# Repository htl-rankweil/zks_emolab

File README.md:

emolab is a new control board hardware with some generic function to run and control
a model car (Carrera 1:24 style) that runs on a Carrera slotcar track.

The boards generic blocks and functionality:

- a Nordic NRF54L15 module form ezurio as core element for communication. preprogrammed with generic SW.
- an Atmega32 processor for easy maintainability by students not familiar with the zephyr system
- both processors interchange information via UART
- the board is supplied from a battery in the range of 10-20V (defined later)
- the processors each have their own LDO as power supply
- an integrated Full Bridge from Toshiba acts as motor driver for speed and direction control
- PWMs can be generated from both cores (selectable via resistor fitting)
- the board has two expansion ports to add further functionality
- the ports have all power lines and a large range of additional IO pins
- I2C and SPI are both available from both cores on the ports. The cores are selected via solder jumper
- The battery voltage can be disconnected from the driver via a PCH Mosfet
- LEDs are provided for each core and to indicate motor supply voltage is on
- The expansion port pins are such that the small standard OLED Display can be fitted directly to have a display either for ATM or from NRF

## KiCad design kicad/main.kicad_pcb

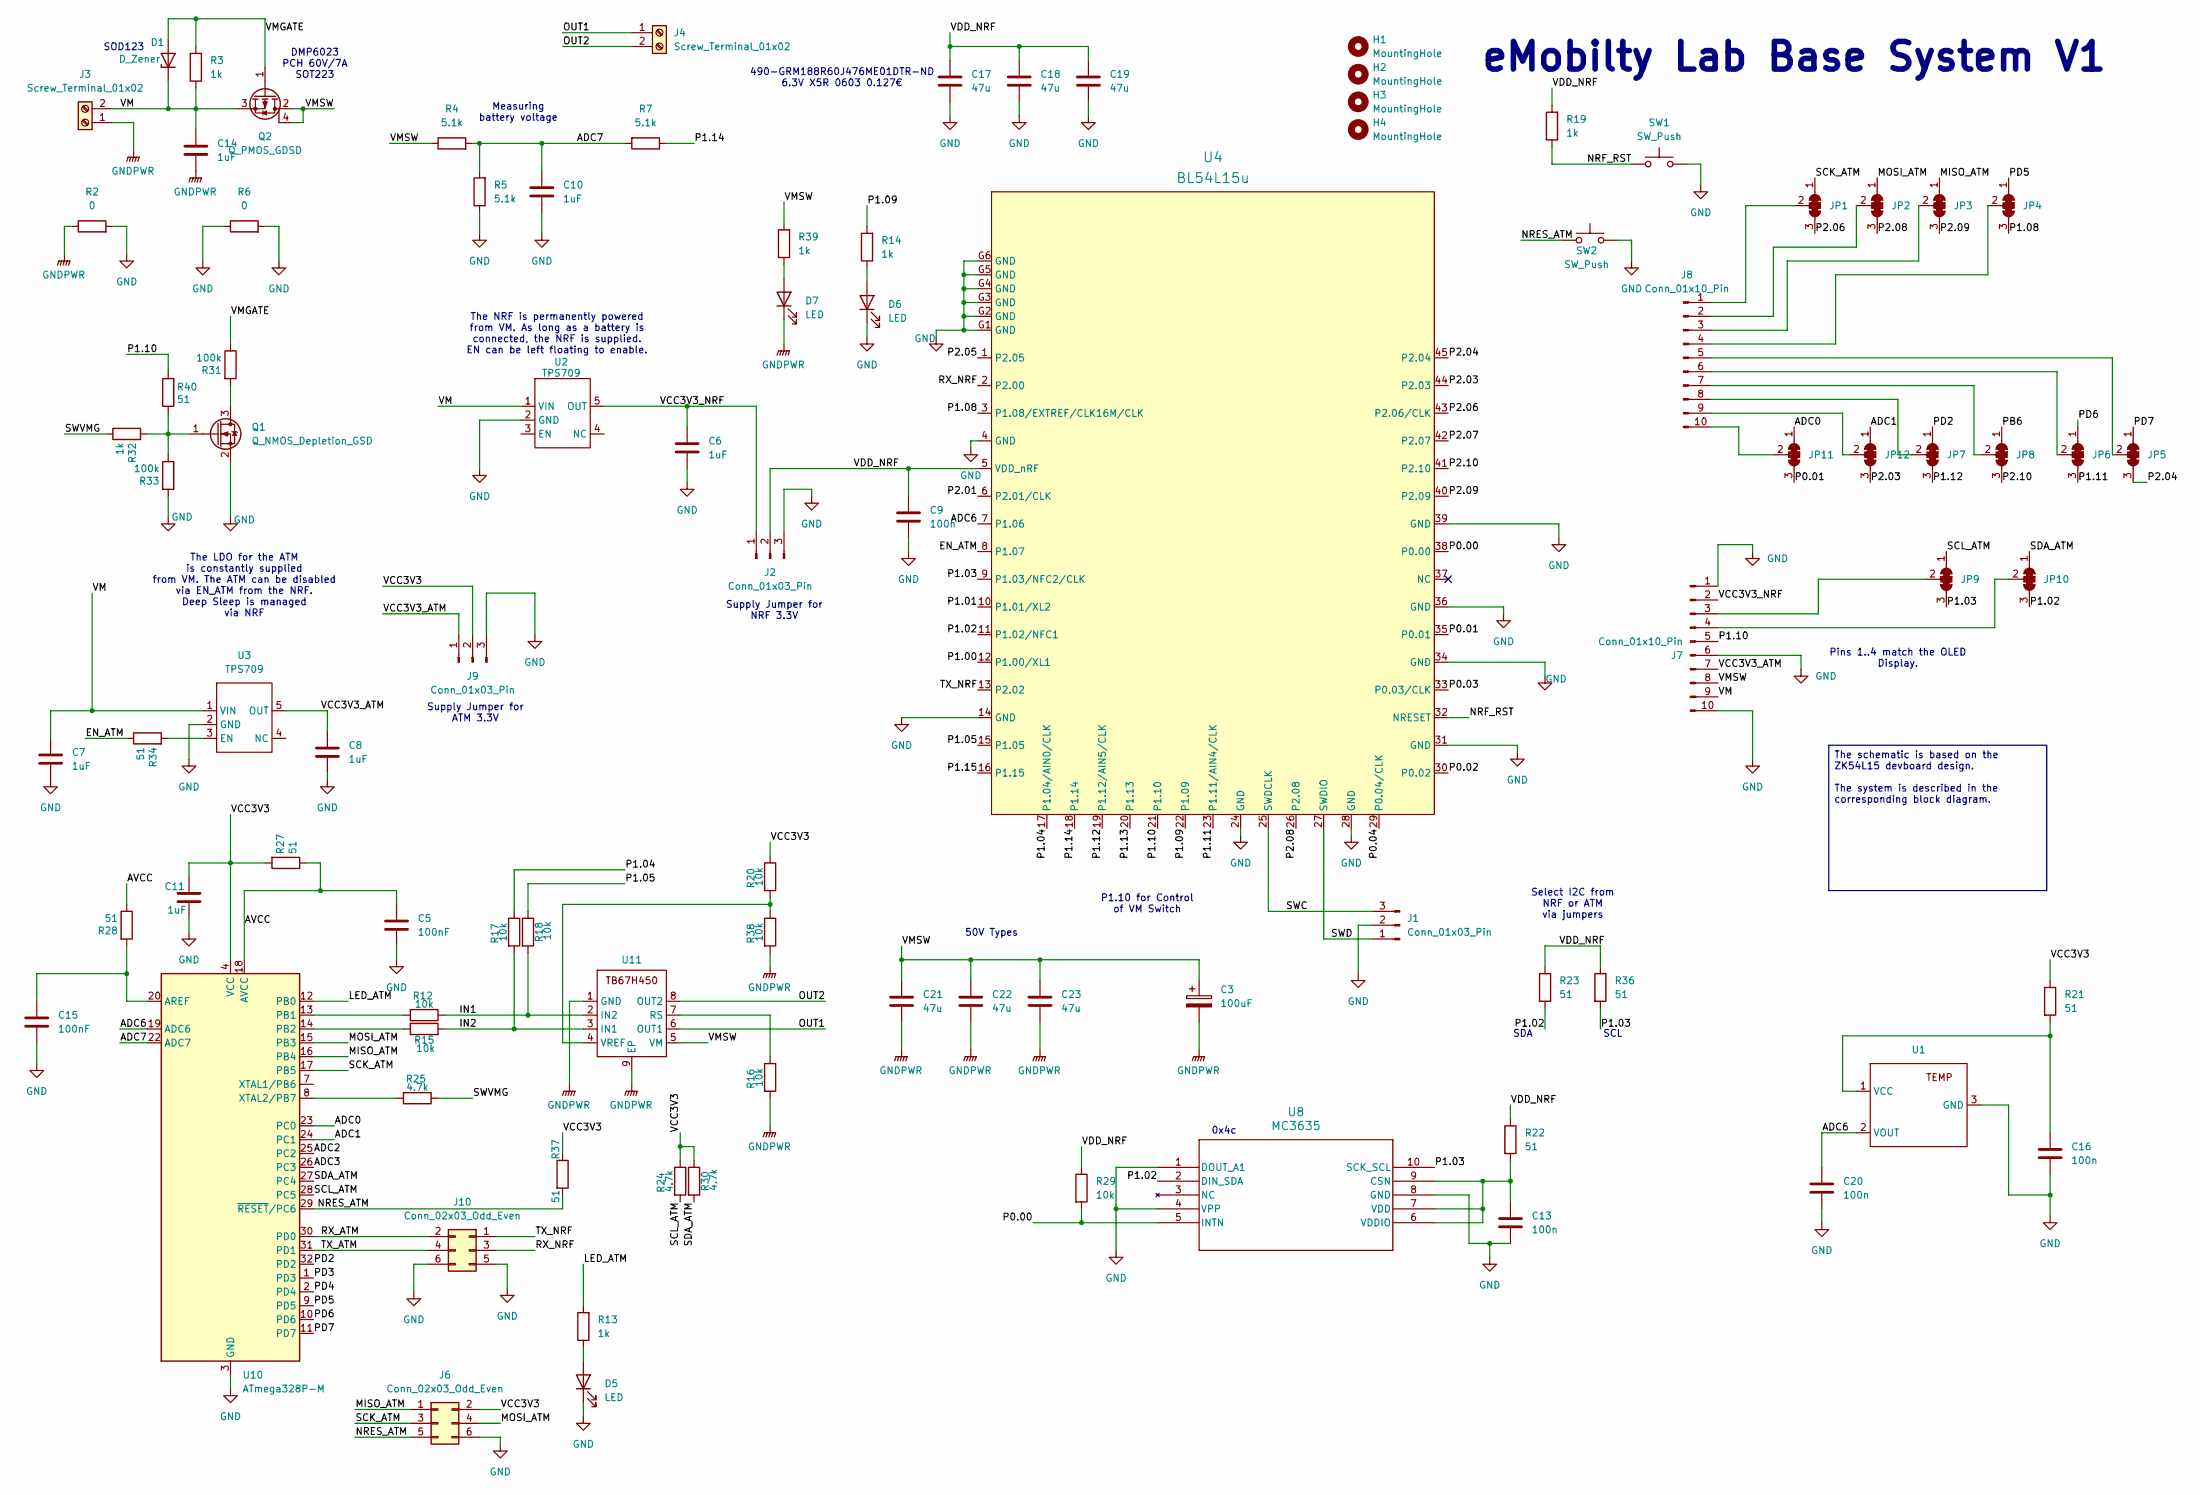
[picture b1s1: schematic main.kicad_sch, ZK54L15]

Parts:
C3: 100uF; C_Radial_D6.3mm_H7.0mm_P2.50mm
C5, C15: 100nF; C_0805_2012Metric_Pad1.18x1.45mm_HandSolder; LCSC C52923
C6, C7, C8, C10, C11, C14: 1uF; C_0805_2012Metric_Pad1.18x1.45mm_HandSolder; LCSC C52923
C9, C13, C16, C20: 100n; C_0805_2012Metric_Pad1.18x1.45mm_HandSolder; LCSC C1525
C17, C18, C19, C21, C22, C23: 47u; C_0805_2012Metric_Pad1.18x1.45mm_HandSolder; LCSC C140782
D1: D_Zener; D_SOD-123
D5: LED; LED_0805_2012Metric_Pad1.15x1.40mm_HandSolder; LCSC C130723
D6, D7: LED; LED_0805_2012Metric_Pad1.15x1.40mm_HandSolder; LCSC C25503856
H1, H2, H3, H4: MountingHole; MountingHole_2.1mm
J1, J2, J9: Conn_01x03_Pin; PinHeader_1x03_P2.54mm_Vertical
J3, J4: Screw_Terminal_01x02; TerminalBlock_Phoenix_MKDS-1,5-2-5.08_1x02_P5.08mm_Horizont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
J6: Conn_02x03_Odd_Even; PinHeader_2x03_P2.54mm_Horizontal
J7, J8: Conn_01x10_Pin; PinHeader_1x10_P2.54mm_Vertical
J10: Conn_02x03_Odd_Even; PinHeader_2x03_P2.54mm_Vertical
JP1, JP2, JP3, JP4, JP5, JP6, JP7, JP8, JP9, JP10, JP11, JP12: SolderJumper_3_Bridged123; SolderJumper-3_P1.3mm_Bridged123_RoundedPad1.0x1.5mm
Q1: Q_NMOS_Depletion_GSD; SOT-23
Q2: Q_PMOS_GDSD; SOT-223
R2: 0; R_0805_2012Metric_Pad1.20x1.40mm_HandSolder
R3: 1k; R_0805_2012Metric_Pad1.20x1.40mm_HandSolder
R4, R5, R7: 5.1k; R_0805_2012Metric_Pad1.20x1.40mm_HandSolder; LCSC C25905
R6: 0; TestGnd_Small
R12, R15, R17, R18, R20, R29, R38: 10k; R_0805_2012Metric_Pad1.20x1.40mm_HandSolder; LCSC C25744
R13, R14, R19, R39: 1k; R_0805_2012Metric_Pad1.20x1.40mm_HandSolder; LCSC C11702
R16: 10k; R_1206_3216Metric_Pad1.30x1.75mm_HandSolder; LCSC C25744
R21, R22, R23, R36: 51; R_0805_2012Metric_Pad1.20x1.40mm_HandSolder; LCSC C25125
R24, R25, R30: 4.7k; R_0805_2012Metric_Pad1.20x1.40mm_HandSolder; LCSC C25744
R27, R28, R34, R40: 51; R_0805_2012Metric_Pad1.20x1.40mm_HandSolder; LCSC C25741
R31, R33: 100k; R_0805_2012Metric_Pad1.20x1.40mm_HandSolder; LCSC C25741
R32: 1k; R_0805_2012Metric_Pad1.20x1.40mm_HandSolder; LCSC C25741
R37: 51; R_0805_2012Metric_Pad1.20x1.40mm_HandSolder; LCSC C25744
SW1, SW2: SW_Push; std_tactile_2
U1: SOT-23
U2, U3: TPS709; SOT-23-5_HandSoldering
U4: BL54L15u; BL54L15U
U8: MC3635; MC3635_MEM; LCSC C3040827
U10: ATmega328P-M; QFN-32-1EP_5x5mm_P0.5mm
U11: SOIC-8-1EP_3.9x4.9mm_P1.27mm_EP2.29x3mm_ThermalVias

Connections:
/ADC0: JP11.1 (A), U10.23 (PC0)
/ADC1: JP12.1 (A), U10.24 (PC1)
/ADC2: U10.25 (PC2)
/ADC3: U10.26 (PC3)
/ADC6: C20.1, U1.2 (VOUT), U4.7 (P1.06), U10.19 (ADC6)
/ADC7: C10.1, R4.2, R5.2, R7.2, U10.22 (ADC7)
/AVCC: C5.1, R27.1, R28.1, U10.18 (AVCC)
/EN_ATM: R34.1, U4.8 (P1.07)
/IN1: R12.1, R18.2, U11.2 (IN2)
/IN2: R15.1, R17.2, U11.3 (IN1)
/LED_ATM: R13.2, U10.12 (PB0)
/MISO_ATM: J6.1, JP3.1 (A), U10.16 (PB4)
/MOSI_ATM: J6.4, JP2.1 (A), U10.15 (PB3)
/NRES_ATM: J6.5, R37.2, SW2.1, U10.29 (~RESET/PC6)
/NRF_RST: R19.1, SW1.1, U4.32 (NRESET)
/OUT1: J4.1, U11.6 (OUT1)
/OUT2: J4.2, U11.8 (OUT2)
/P0.00: R29.2, U4.38 (P0.00), U8.5 (INTN)
/P0.01: JP11.3 (B), U4.35 (P0.01)
/P0.02: U4.30 (P0.02)
/P0.03: U4.33 (P0.03/CLK)
/P0.04: U4.29 (P0.04/CLK)
/P1.00: U4.12 (P1.00/XL1)
/P1.01: U4.10 (P1.01/XL2)
/P1.02: JP10.3 (B), R23.2, U4.11 (P1.02/NFC1), U8.2 (DIN_SDA)
/P1.03: JP9.3 (B), R36.2, U4.9 (P1.03/NFC2/CLK), U8.10 (SCK_SCL)
/P1.04: R17.1, U4.17 (P1.04/AIN0/CLK)
/P1.05: R18.1, U4.15 (P1.05)
/P1.08: JP4.3 (B), U4.3 (P1.08/EXTREF/CLK16M/CLK)
/P1.09: R14.2, U4.22 (P1.09)
/P1.10: J7.5, R40.2, U4.21 (P1.10)
/P1.11: JP6.3 (B), U4.23 (P1.11/AIN4/CLK)
/P1.12: JP7.3 (B), U4.19 (P1.12/AIN5/CLK)
/P1.13: U4.20 (P1.13)
/P1.14: R7.1, U4.18 (P1.14)
/P1.15: U4.16 (P1.15)
/P2.01: U4.6 (P2.01/CLK)
/P2.03: JP12.3 (B), U4.44 (P2.03)
/P2.04: JP5.3 (B), U4.45 (P2.04)
/P2.05: U4.1 (P2.05)
/P2.06: JP1.3 (B), U4.43 (P2.06/CLK)
/P2.07: U4.42 (P2.07)
/P2.08: JP2.3 (B), U4.26 (P2.08)
/P2.09: JP3.3 (B), U4.40 (P2.09)
/P2.10: JP8.3 (B), U4.41 (P2.10)
/PB6: JP8.1 (A)
/PD2: JP7.1 (A), U10.32 (PD2)
/PD3: U10.1 (PD3)
/PD4: U10.2 (PD4)
/PD5: JP4.1 (A), U10.9 (PD5)
/PD6: JP6.1 (A), U10.10 (PD6)
/PD7: JP5.1 (A), U10.11 (PD7)
/RX_ATM: J10.2, U10.30 (PD0)
/RX_NRF: J10.3, U4.2 (P2.00)
/SCK_ATM: J6.3, JP1.1 (A), U10.17 (PB5)
/SCL_ATM: JP9.1 (A), R24.2, U10.28 (PC5)
/SDA_ATM: JP10.1 (A), R30.2, U10.27 (PC4)
/SWC: J1.3, U4.25 (SWDCLK)
/SWD: J1.1, U4.27 (SWDIO)
/SWVMG: R25.1, R32.1
/TX_ATM: J10.4, U10.31 (PD1)
/TX_NRF: J10.1, U4.13 (P2.02)
/VCC3V3: C11.1, J6.2, J9.2, R20.1, R21.1, R24.1, R27.2, R30.1, R37.1, U10.4 (VCC), U10.6 (VCC)
/VCC3V3_ATM: C8.1, J7.7, J9.1, U3.5 (OUT)
/VCC3V3_NRF: C6.1, J2.1, J7.2, U2.5 (OUT)
/VDD_NRF: C9.1, C17.1, C18.1, C19.1, J2.2, R19.2, R22.1, R23.1, R29.1, R36.1, U4.5 (VDD_nRF)
/VM: C7.1, C14.1, D1.1 (K), J3.2, J7.9, Q2.3 (S), R3.1, U2.1 (VIN), U3.1 (VIN)
/VMGATE: D1.2 (A), Q2.1 (G), R3.2, R31.1
/VMSW: C3.1, C21.1, C22.1, C23.1, J7.8, Q2.2 (D), Q2.4 (D), R4.1, R39.2, U11.5 (VM)
GND: C5.2, C6.2, C7.2, C8.2, C9.2, C10.2, C11.2, C13.2, C15.2, C16.2, C17.2, C18.2, C19.2, C20.2, D5.1 (K), D6.1 (K), J1.2, J2.3, J6.6, J7.1, J7.6, J7.10, J9.3, J10.5, J10.6, Q1.2 (S), R2.2, R5.1, R6.1, R6.2, R33.2, SW1.2, SW2.2, U1.3 (GND), U2.2 (GND), U3.2 (GND), U4.4 (GND), U4.14 (GND), U4.24 (GND), U4.28 (GND), U4.31 (GND), U4.34 (GND), U4.36 (GND), U4.39 (GND), U4.G1 (GND), U4.G2 (GND), U4.G3 (GND), U4.G4 (GND), U4.G5 (GND), U4.G6 (GND), U8.1 (DOUT_A1), U8.4 (VPP), U8.8 (GND), U10.3 (GND), U10.5 (GND), U10.21 (GND)
GNDPWR: C3.2, C14.2, C21.2, C22.2, C23.2, D7.1 (K), J3.1, R2.1, R16.2, R38.2, U11.1 (GND), U11.9 (EP)
unnamed: D5.2 (A), R13.1
unnamed: D6.2 (A), R14.1
unnamed: D7.2 (A), R39.1
unnamed: J7.3, JP9.2 (C)
unnamed: J7.4, JP10.2 (C)
unnamed: J8.1, JP1.2 (C)
unnamed: J8.2, JP2.2 (C)
unnamed: J8.3, JP3.2 (C)
unnamed: J8.4, JP4.2 (C)
unnamed: J8.5, JP5.2 (C)
unnamed: J8.6, JP6.2 (C)
unnamed: J8.7, JP8.2 (C)
unnamed: J8.8, JP7.2 (C)
unnamed: J8.9, JP12.2 (C)
unnamed: J8.10, JP11.2 (C)
unnamed: Q1.3 (D), R31.2
unnamed: Q1.1 (G), R32.2, R33.1, R40.1
unnamed: C16.1, R21.2, U1.1 (VCC)
unnamed: R34.2, U3.3 (EN)
unnamed: C13.1, R22.2, U8.6 (VDDIO), U8.7 (VDD), U8.9 (CSN)
unnamed: C15.1, R28.2, U10.20 (AREF)
unnamed: R12.2, U10.13 (PB1)
unnamed: R15.2, U10.14 (PB2)
unnamed: R25.2, U10.8 (XTAL2/PB7)
unnamed: R16.1, U11.7 (RS)
unnamed: R20.2, R38.1, U11.4 (VREF)

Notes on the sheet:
Supply Jumper for NRF 3.3V
0x4c
SCL
P1.10 for Control of VM Switch
DMP6023 PCH 60V/7A SOT223
Select I2C from NRF or ATM via jumpers
50V Types
Pins 1..4 match the OLED Display.
eMobilty Lab Base System V1
SOD123
490-GRM188R60J476ME01DTR-ND 6.3V X5R 0603 0.127€
Supply Jumper for ATM 3.3V
SDA
The NRF is permanently powered from VM. As long as a battery is connected, the NRF is supplied. EN can be left floating to enable.
Measuring battery voltage
The LDO for the ATM is constantly supplied from VM. The ATM can be disabled via EN_ATM from the NRF. Deep Sleep is managed via NRF
The schematic is based on the ZK54L15 devboard design. The system is described in the corresponding block diagram.

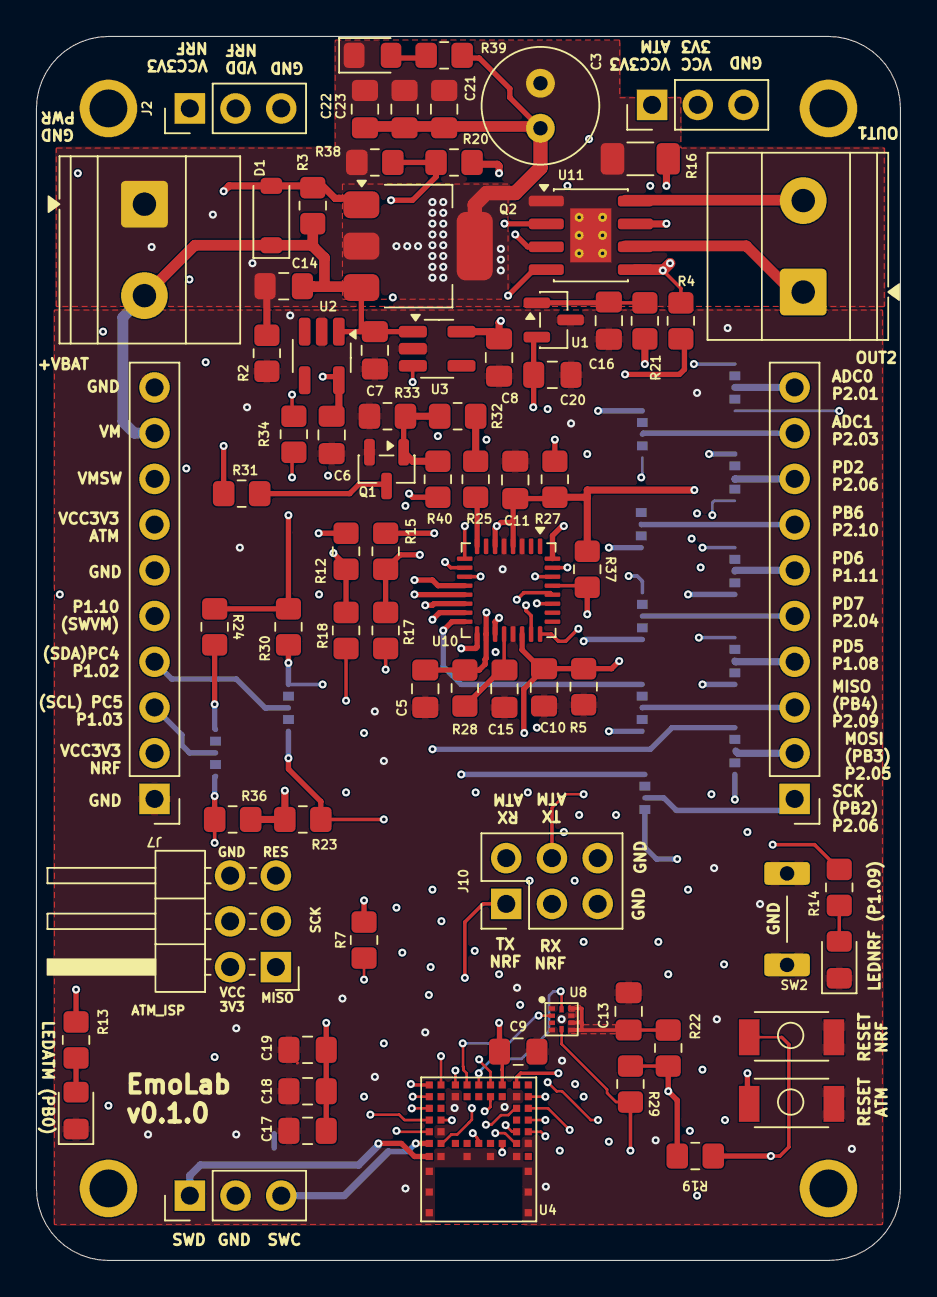
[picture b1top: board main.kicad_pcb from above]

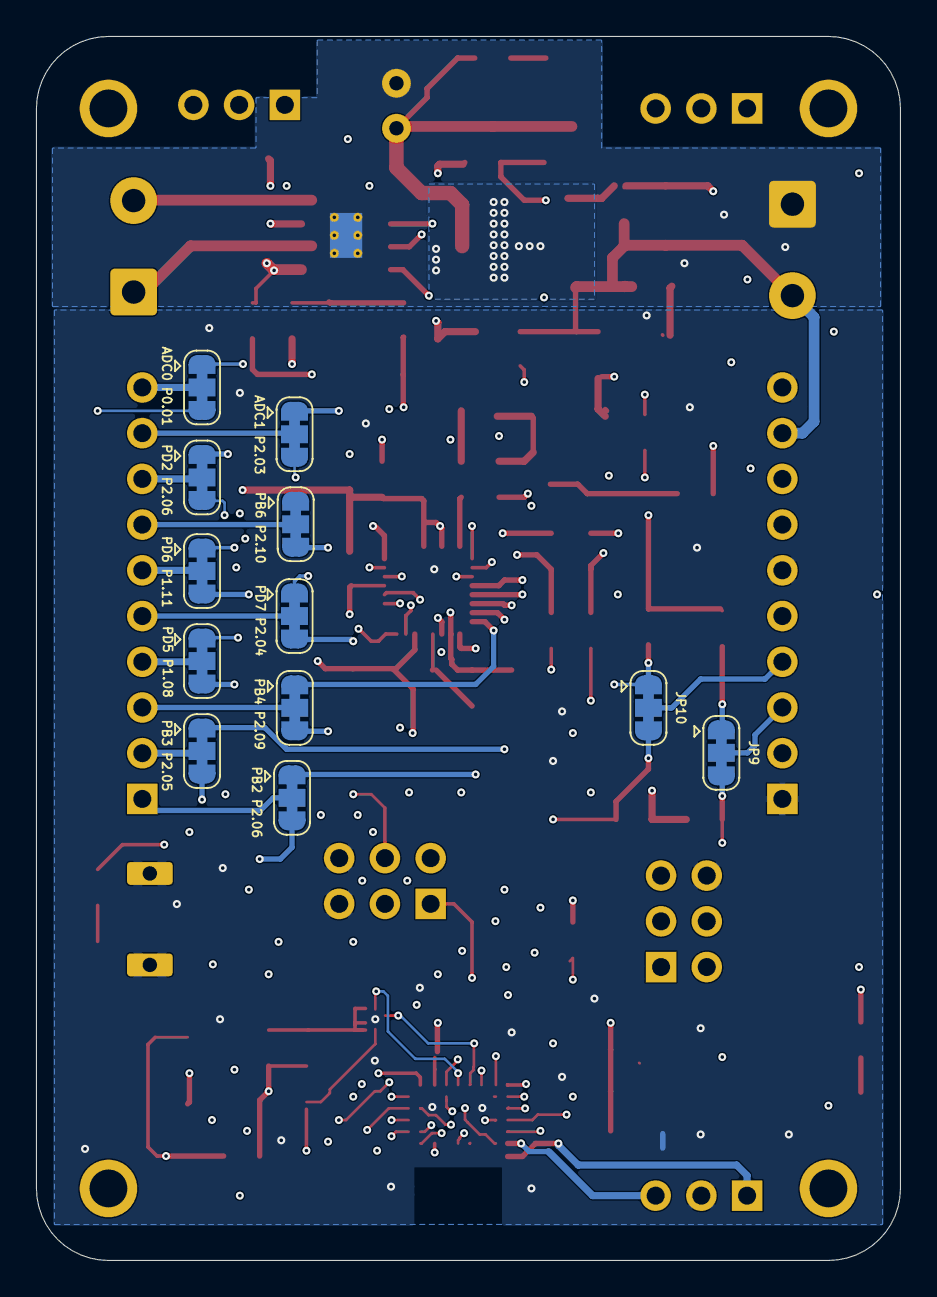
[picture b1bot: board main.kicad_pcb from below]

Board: 4 copper layers, 48.0 x 68.0 mm, 92 parts (12 on the bottom side), 82 nets.

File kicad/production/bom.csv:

Designator,Footprint,Quantity,Value,LCSC Part #
"C10, C11, C14, C6, C7, C8",0805,6,1uF,C52923
"C13, C16, C20, C9",0805,4,100n,C1525
"C15, C5",0805,2,100nF,C52923
"C17, C18, C19, C21, C22, C23",0805,6,47u,C140782
C3,C_Radial_D6.3mm_H7.0mm_P2.50mm,1,100uF,
D1,D_SOD-123,1,D_Zener,
D5,0805,1,LED,C130723
"D6, D7",0805,2,LED,C25503856
"J1, J2, J9",PinHeader_1x03_P2.54mm_Vertical,3,Conn_01x03_Pin,
J10,PinHeader_2x03_P2.54mm_Vertical,1,Conn_02x03_Odd_Even,
"J3, J4","TerminalBlock_Phoenix_MKDS-1,5-2-5.08_1x02_P5.08mm_Horizontal",2,Screw_Terminal_01x02,
J6,PinHeader_2x03_P2.54mm_Horizontal,1,Conn_02x03_Odd_Even,
"J7, J8",PinHeader_1x10_P2.54mm_Vertical,2,Conn_01x10_Pin,
Q1,SOT-23,1,Q_NMOS_Depletion_GSD,
Q2,SOT-223,1,Q_PMOS_GDSD,
"R12, R15, R17, R18, R20, R29, R38",0805,7,10k,C25744
"R13, R14, R19, R39",0805,4,1k,C11702
R16,1206,1,10k,C25744
R2,0805,1,0,
"R21, R22, R23, R36",0805,4,51,C25125
"R24, R25, R30",0805,3,4.7k,C25744
"R27, R28, R34, R40",0805,4,51,C25741
R3,0805,1,1k,
"R31, R33",0805,2,100k,C25741
R32,0805,1,1k,C25741
R37,0805,1,51,C25744
"R4, R5, R7",0805,3,5.1k,C25905
R6,TestGnd_Small,1,0,
"SW1, SW2",std_tactile_2,2,SW_Push,
U1,SOT-23,1,~,
U10,QFN-32-1EP_5x5mm_P0.5mm,1,ATmega328P-M,
U11,SOIC-8-1EP_3.9x4.9mm_P1.27mm_EP2.29x3mm_ThermalVias,1,~,
"U2, U3",SOT-23-5_HandSoldering,2,TPS709,
U4,BL54L15U,1,BL54L15u,
U8,MC3635_MEM,1,MC3635,C3040827
